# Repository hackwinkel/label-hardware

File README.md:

# label-hardware

The "label" is a cheap badge with a PADAUK PFS154-S16 microcontroller, 40 leds and IR transmitter & receiver for inter-badge communications.
The software/hardware *may* also work with a PMS150C-S16 and pin compatible controllers from other manufacturers (e.g. Nyquest tech), but this is untested

This hardware goes with the software described here: https://github.com/hackwinkel/label-software

## Background

This badge was originally designed for SMD hotplate soldering workshops at TBD (https://tbd.camp/) and later used for workshops at bornhack 2023 () and private workshops

According to internet rule 663829, "Every hacker conference shall have a badge". Being hackers, of course, leads to hypotheses 1-3:
"1: Any hacker conference badge will be overly complex",
"2: Any hacker conference badge will be released with unfinished software" and
"3: Any hacker conference  badge will function poorly for its namesake purpose".
This badge disproves these 3 hypotheses.

## What is in this repository

0) This README
1) a LICENSE file
2) A directory with KiCAD 5 source files
3) A directory with PCB fabrication (Gerber) files produced from these source files
4) A ZIP file containing the Gerber files for PCB fabrication.
5) A director with stencil fabrication (Gerber) files, with 4 copies of the stencil (will fit on a single laser-cut stencil)
6) A ZIP file containing the Gerber files for stencil fabrication.
7) A parts list

If you only want to produce PCBs, you should be able to upload the PCB_fabrication.zip file to your PCB board house directly.
If you want to produce a single stencil, you can use  the PCB_fabrication.zip file - yoor PCB board house will extract the right file from this.
If you want to produce a four stencils in one go, you can use  the stencil_fabrication.zip file.

As the board only contains SMD components on the front side, you have to specify that the PCB board house should make a stencil from the "front paste" Gerber file only

## Reprogramming in-circuit

Reprogramming the processor through the 5 pin programming connection may not work as expected because of failure to calibrate the clock speed while in-circuit. You CAN reprogram the badge without clock-speed calibration by using easypdkprog with the --nocalibrate option.

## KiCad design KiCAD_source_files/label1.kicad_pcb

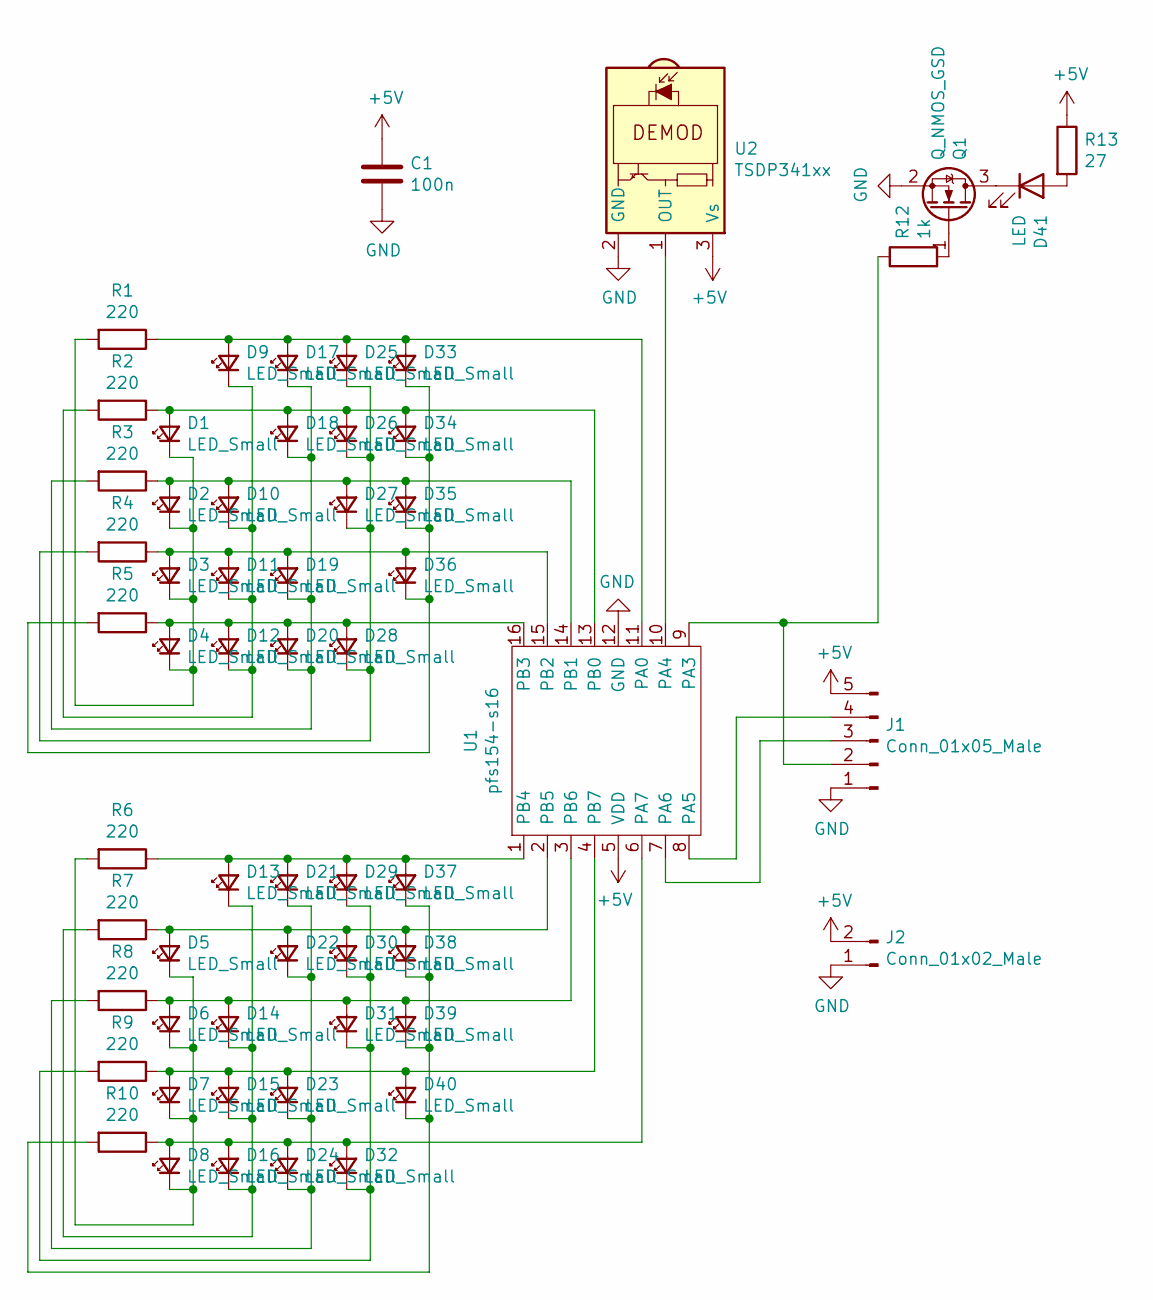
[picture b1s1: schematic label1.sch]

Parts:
C1: 100n; C_0805
D1, D2, D3, D4, D5, D6, D7, D8, D9, D10, D11, D12, D13, D14, D15, D16, D17, D18, D19, D20, D21, D22, D23, D24, D25, D26, D27, D28, D29, D30, D31, D32, D33, D34, D35, D36, D37, D38, D39, D40: LED_Small; D_0805
D41: LED; LED_2835
J1: Conn_01x05_Male; PinHeader_1x05
J2: Conn_01x02_Male; battcon
Q1: Q_NMOS_GSD; SOT-23
R1, R2, R3, R4, R5, R6, R7, R8, R9, R10: 220; R_0805
R12: 1k; R_0805
R13: 27; R_1206
U1: pfs154-s16; SOP-16
U2: TSDP341xx; IR_receiver

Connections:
+5V: C1.1, J1.5, J2.2, R13.1, U1.5 (VDD), U2.3 (Vs)
GND: C1.2, J1.1, J2.1, Q1.2 (S), U1.12 (GND), U2.2 (GND)
unnamed: D1.1 (K), D2.1 (K), D3.1 (K), D4.1 (K), R1.2
unnamed: D1.2 (A), D18.2 (A), D26.2 (A), D34.2 (A), R2.1, U1.13 (PB0)
unnamed: D5.1 (K), D6.1 (K), D7.1 (K), D8.1 (K), R6.2
unnamed: D9.1 (K), D10.1 (K), D11.1 (K), D12.1 (K), R2.2
unnamed: D2.2 (A), D10.2 (A), D27.2 (A), D35.2 (A), R3.1, U1.14 (PB1)
unnamed: D3.2 (A), D11.2 (A), D19.2 (A), D36.2 (A), R4.1, U1.15 (PB2)
unnamed: D4.2 (A), D12.2 (A), D20.2 (A), D28.2 (A), R5.1, U1.16 (PB3)
unnamed: D13.1 (K), D14.1 (K), D15.1 (K), D16.1 (K), R7.2
unnamed: D13.2 (A), D21.2 (A), D29.2 (A), D37.2 (A), R6.1, U1.1 (PB4)
unnamed: D6.2 (A), D14.2 (A), D31.2 (A), D39.2 (A), R8.1, U1.3 (PB6)
unnamed: D7.2 (A), D15.2 (A), D23.2 (A), D40.2 (A), R9.1, U1.4 (PB7)
unnamed: D8.2 (A), D16.2 (A), D24.2 (A), D32.2 (A), R10.1, U1.6 (PA7)
unnamed: D17.1 (K), D18.1 (K), D19.1 (K), D20.1 (K), R3.2
unnamed: D9.2 (A), D17.2 (A), D25.2 (A), D33.2 (A), R1.1, U1.11 (PA0)
unnamed: D21.1 (K), D22.1 (K), D23.1 (K), D24.1 (K), R8.2
unnamed: D5.2 (A), D22.2 (A), D30.2 (A), D38.2 (A), R7.1, U1.2 (PB5)
unnamed: D25.1 (K), D26.1 (K), D27.1 (K), D28.1 (K), R4.2
unnamed: D29.1 (K), D30.1 (K), D31.1 (K), D32.1 (K), R9.2
unnamed: D33.1 (K), D34.1 (K), D35.1 (K), D36.1 (K), R5.2
unnamed: D37.1 (K), D38.1 (K), D39.1 (K), D40.1 (K), R10.2
unnamed: D41.1 (K), Q1.3 (D)
unnamed: D41.2 (A), R13.2
unnamed: J1.2, R12.1, U1.9 (PA3)
unnamed: J1.3, U1.7 (PA6)
unnamed: J1.4, U1.8 (PA5)
unnamed: Q1.1 (G), R12.2
unnamed: U1.10 (PA4), U2.1 (OUT)

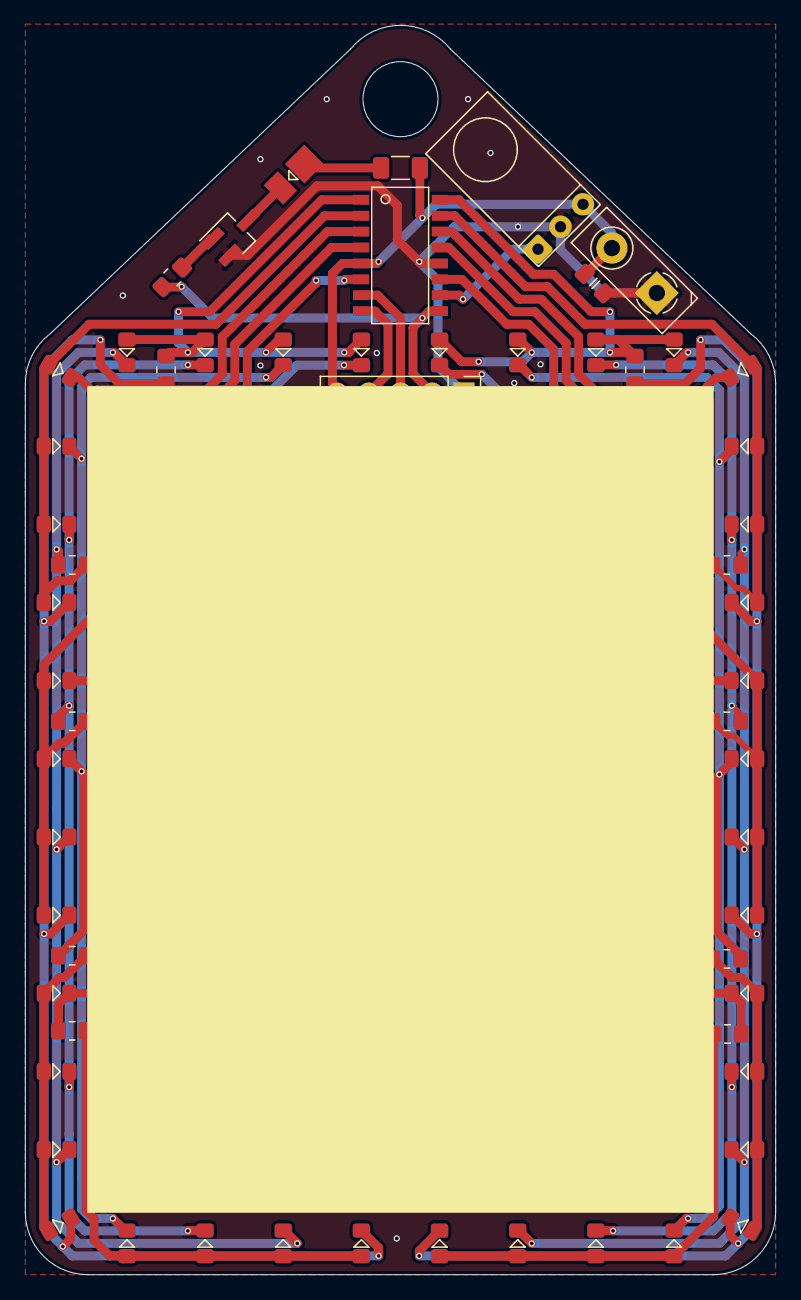
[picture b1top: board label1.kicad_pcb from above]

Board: 2 copper layers, 60.0 x 99.9 mm, 59 parts (0 on the bottom side), 29 nets.

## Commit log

2023-08-15 Initial commit of the label hardware design and documentation
2023-08-15 fix typo
2023-08-15 Fix formatting
2023-08-15 added list of parts

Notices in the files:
KiCAD_source_files/label1.kicad_pcb:
(c)2023 Theo Borm
